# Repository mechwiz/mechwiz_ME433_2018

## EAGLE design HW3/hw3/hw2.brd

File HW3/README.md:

# ME-433 HW3
**Michael Wizniter**

1. Overall PCB:

2. Top PCB:

3. Bottom PCB:

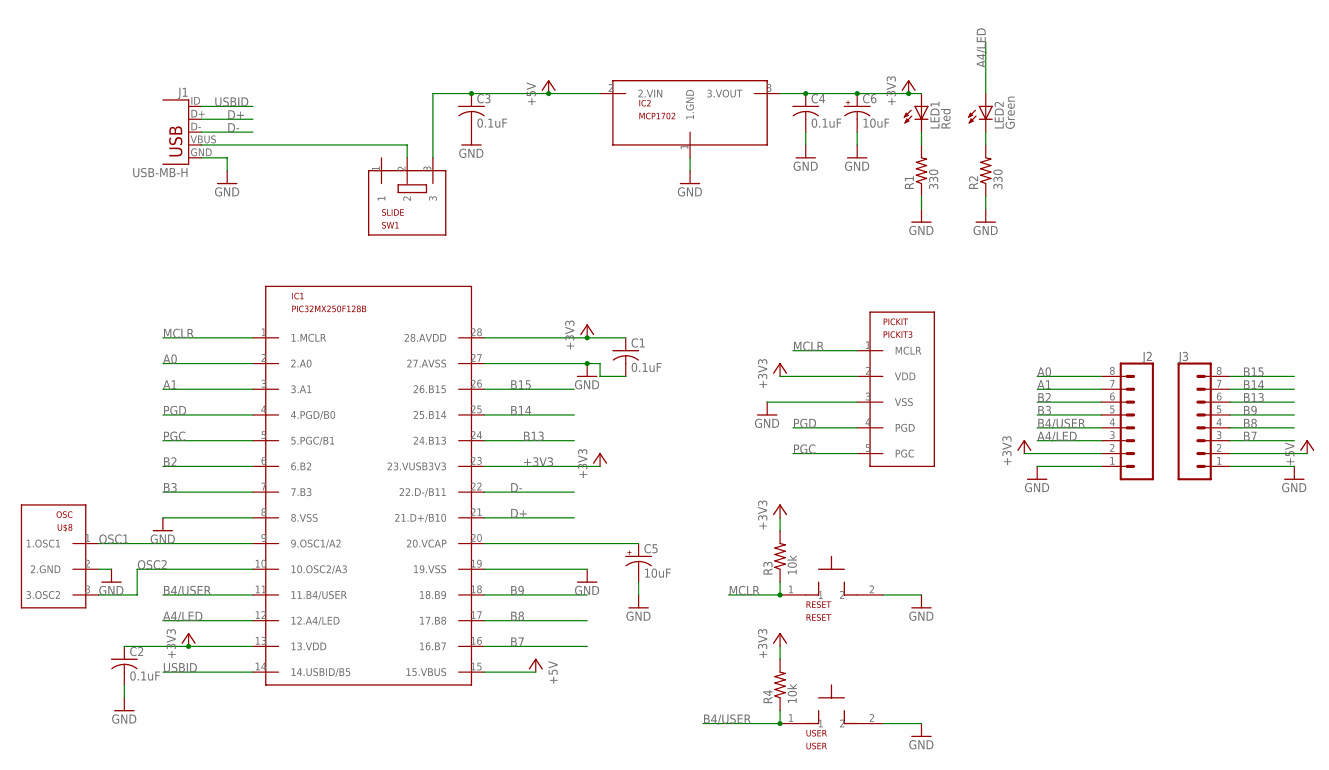
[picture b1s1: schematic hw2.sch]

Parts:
C1, C2, C3, C4: 0.1uF; C025-025X050
C5, C6: 10uF; B45181B
IC1: PIC32MX250F128B; DIL28-3
IC2: MCP1702; TO92
J1: USB-MB-H
J2, J3: CONN_08"; 1X08
LED1: Red; LED3MM
LED2: Green; LED3MM
PICKIT: PICKIT3; 1X05
R1, R2: 330; 0207/10
R3, R4: 10k; 0207/10
RESET: RESET; PB
SW1: SLIDE
U$8: OSC
USER: USER; PB

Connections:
+3V3: C1.1, C2.1, C4.1, C6.+, IC1.13 (13.VDD), IC1.23 (23.VUSB3V3), IC1.28 (28.AVDD), IC2.3 (3.VOUT), J2.2, LED1.A, PICKIT.2 (VDD), R3.2, R4.2
+5V: C3.1, IC1.15 (15.VBUS), IC2.2 (2.VIN), J3.2, SW1.3
A0: IC1.2 (2.A0), J2.8
A1: IC1.3 (3.A1), J2.7
A4/LED: IC1.12 (12.A4/LED), J2.3, LED2.A
B2: IC1.6 (6.B2), J2.6
B3: IC1.7 (7.B3), J2.5
B4/USER: IC1.11 (11.B4/USER), J2.4, R4.1, USER.1
B7: IC1.16 (16.B7), J3.3
B8: IC1.17 (17.B8), J3.4
B9: IC1.18 (18.B9), J3.5
B13: IC1.24 (24.B13), J3.6
B14: IC1.25 (25.B14), J3.7
B15: IC1.26 (26.B15), J3.8
D+: IC1.21 (21.D+/B10), J1.D+
D-: IC1.22 (22.D-/B11), J1.D-
GND: C1.2, C2.2, C3.2, C4.2, C5.-, C6.-, IC1.8 (8.VSS), IC1.19 (19.VSS), IC1.27 (27.AVSS), IC2.1 (1.GND), J1.GND, J2.1, J3.1, PICKIT.3 (VSS), R1.1, R2.1, RESET.2, U$8.2 (2.GND), USER.2
MCLR: IC1.1 (1.MCLR), PICKIT.1 (MCLR), R3.1, RESET.1
unnamed: J1.VBUS, SW1.2
unnamed: LED1.K (C), R1.2
unnamed: LED2.K (C), R2.2
unnamed: C5.+, IC1.20 (20.VCAP)
OSC1: IC1.9 (9.OSC1/A2), U$8.1 (1.OSC1)
OSC2: IC1.10 (10.OSC2/A3), U$8.3 (3.OSC2)
PGC: IC1.5 (5.PGC/B1), PICKIT.5 (PGC)
PGD: IC1.4 (4.PGD/B0), PICKIT.4 (PGD)
USBID: IC1.14 (14.USBID/B5), J1.ID

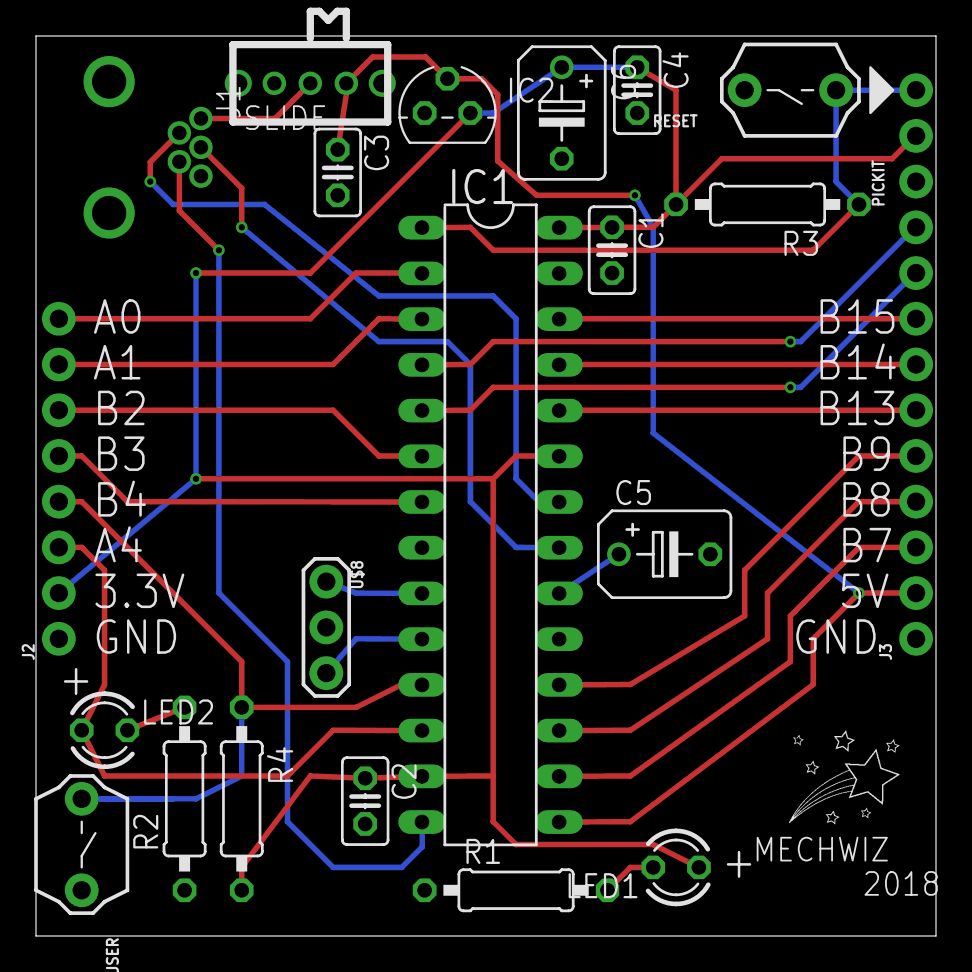
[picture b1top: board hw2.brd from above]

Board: 2 copper layers, 50.0 x 50.0 mm, 22 parts (0 on the bottom side), 27 nets.

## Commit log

2018-04-10 created repo
2018-04-10 drew circuit diagram
2018-04-10 took screen-shot of oscillations
2018-04-10 took screen-shot of clean voltage. occured after adding cap between output and ground
2018-04-10 took photo of breadboard with all wiring done
2018-04-10 Created new project
2018-04-10 initialized the pragmas
2018-04-10 got the code working at the right frequecy
2018-04-10 updated FPLLIDIV and delay time for ticks in the loop. realized that the timer was based off of 48MHz instead of 8Mhz
2018-04-10 added some comments
2018-04-10 added readme to HW1
2018-04-10 fixed typo
2018-04-11 copied all existing libraries and updated usb symbol
2018-04-12 Finished creating and adding parts to library
2018-04-12 created schematic
2018-04-12 updated some names on schematic and created first draft of board
2018-04-12 finished wiring board
2018-04-13 updated board with annotations
2018-04-13 added bmp to board
2018-04-15 updated board layout and generated gerber files
2018-04-15 updated gerber files
2018-04-15 updated tag placement and regenerated gerber files
2018-04-15 added imgs and readme
2018-04-15 changed name of gerber files
2018-04-19 started HW4 project
2018-04-19 finished up functions besides for main
2018-04-19 created main loop
2018-04-19 completed HW4. added readme with pics
2018-04-20 started coding for HW5
2018-04-22 code is now working
2018-04-22 added comments to HW4
2018-04-22 added comments to HW5
2018-04-22 made schematic. finished hw5
2018-04-22 changed 4 to 5
2018-04-24 created HW6 project
2018-04-24 cleared out some code
2018-04-24 wrote drawChar function
2018-04-24 Hello world is showing up :)
2018-04-24 updated code
2018-04-24 got rid of /0s
2018-04-27 fixed some formatting
2018-04-27 fixed some more formatting
2018-04-27 created HW7 project and added header and main files
2018-04-29 reading values from IMU succesfully
2018-04-29 setup perpendicular axes. working perfectly
2018-04-29 updated formatting
2018-04-29 added comments. changed freq
2018-05-01 created first harmony project and got HW1 to run succesfully
2018-05-01 added in libraries and got HW7 to work :)
2018-05-01 moved prototypes to h file
2018-05-03 created HW9 and confirmed that the default program is working using screen
2018-05-03 added IMU stuff
2018-05-04 updated code to read IMU at 5HZ and output at 100 HZ
2018-05-04 outputs at 100HZ, reads IMU at 5HZ whenever r is pressed
2018-05-04 updated Hw to read IMU at 100HZ instead of 5. everything is working great
2018-05-09 created HW10 project
2018-05-09 updated some HW9 stuff
2018-05-09 apparently forgot to copy the usb stuff into app.h
2018-05-09 HW10 works just like HW9 now except it's with LCD screen
2018-05-10 updated code. working now
2018-05-10 added readme
2018-05-10 fixed formatting
2018-05-10 added explanation
2018-05-11 put together everything for HW11. just need to code now
2018-05-11 put in excel sheet with data
2018-05-11 got default mouse code to work while blinking LED and printing accel values on LCD
2018-05-13 changed code so that mouse is moving in diagonal
2018-05-13 implemented imu for mouse
2018-05-15 got helloworld project to work
2018-05-16 implementd slided bar
2018-05-17 apparently modified this file
2018-05-17 added HW13 project and ran default code succesfully
2018-05-17 added slider
2018-05-17 changed from private to static
2018-05-17 added loop to go through rows
2018-05-17 added threshold check for green-blue > some thresh
2018-05-17 took away some padding
2018-05-22 created CDC framework for HW14
2018-05-22 added in new code from Nick
2018-05-22 didn't change nothing but apparently i did
2018-05-22 created android project and got app to work without usb capability
2018-05-22 added in code for usb communication to PIC
2018-05-22 added code that sends string to the pic
2018-05-28 CAD, DXF, STL, and PNG files for HW15
2018-05-28 formatted readme
2018-05-28 img resize
2018-05-28 resize img
2018-05-29 added image of actual housing
2018-06-13 made red tracker app
2018-06-13 made HW16 project and made sure default CDC code works
2018-06-13 added motor init code
2018-06-13 updated PI control
2018-06-13 updated pi again
2018-06-13 didn't changenothing but whatever
2018-06-13 made PIC code
2018-06-13 made android code
2018-06-13 changed kp value
2018-06-13 did some tuning
2018-06-13 included recover from error capability
2018-06-13 edited lighting exposure settings
2018-06-14 made tweaks that I made in HW18 in HW17
2018-06-14 added vid
2018-06-14 added pics
